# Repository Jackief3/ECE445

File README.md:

# Water Quality Management System

The goal of the project is to manage water quality for life in aquatic environments.

Team members:
- Jackie Fang
- Harrison Griggs
- Haokai Liu

## Results

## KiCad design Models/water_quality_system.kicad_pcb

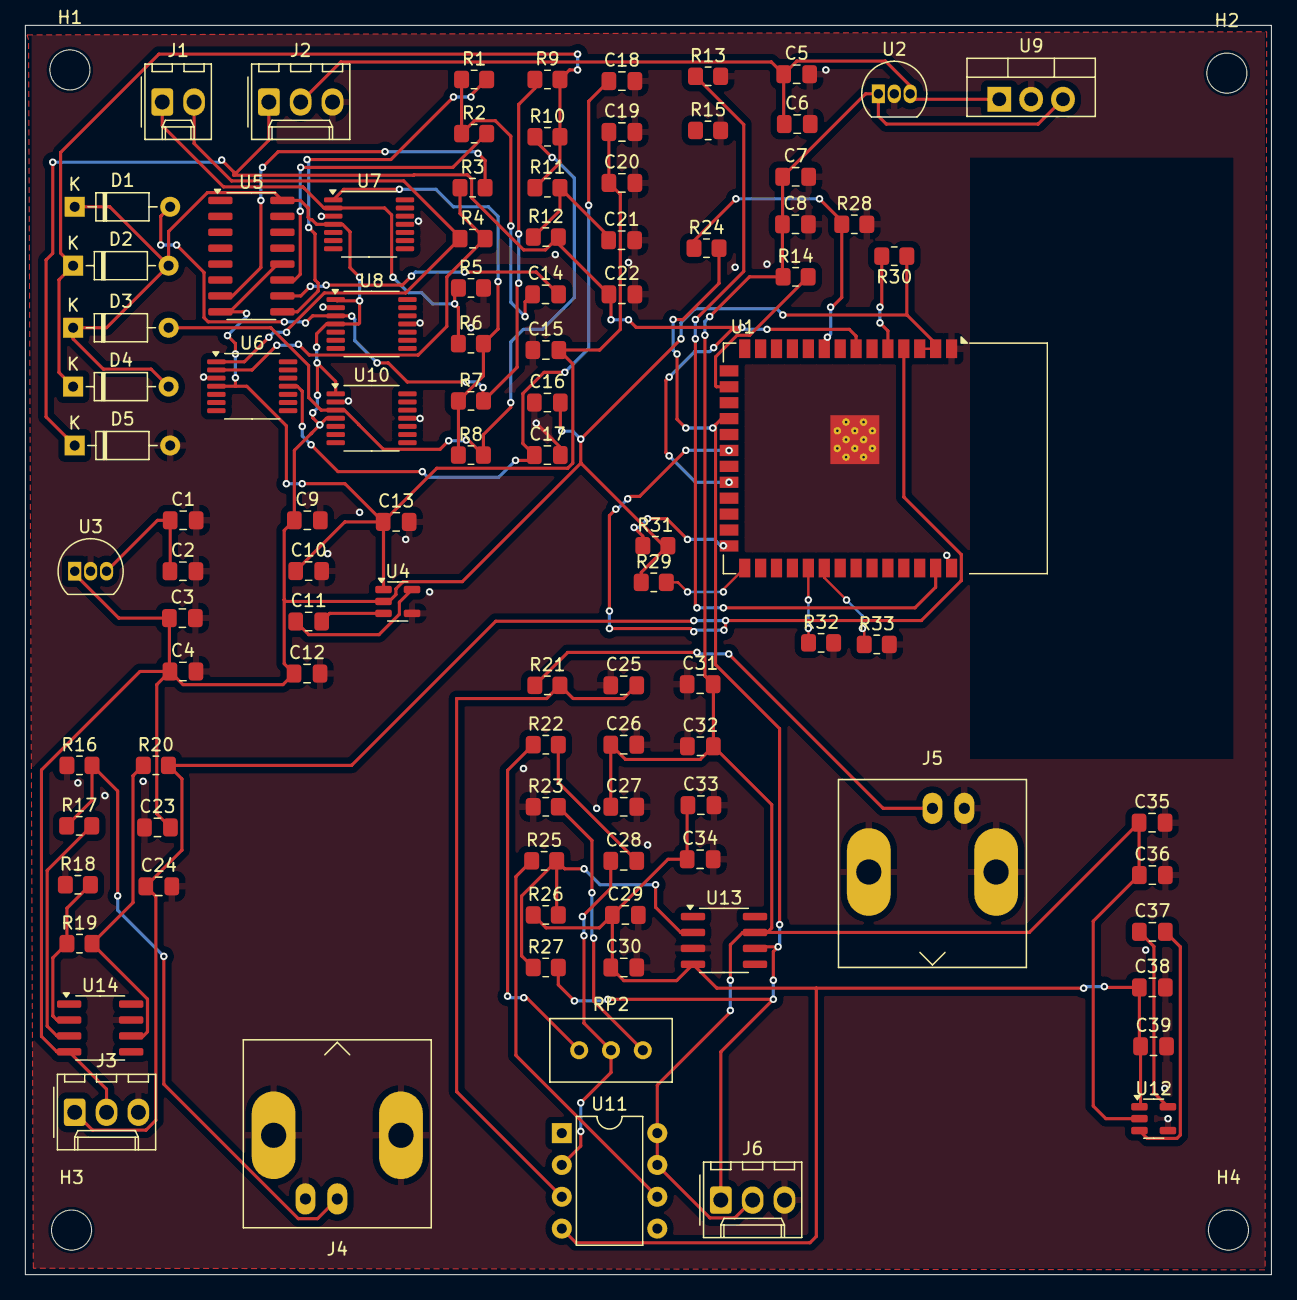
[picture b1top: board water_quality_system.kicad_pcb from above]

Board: 2 copper layers, 99.4 x 99.7 mm, 102 parts (0 on the bottom side), 48 nets.

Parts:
C1, C3, C5, C7, C12, C13, C27, C30, C33, C35, C38: 10uF; C_0805_2012Metric_Pad1.18x1.45mm_HandSolder
C2, C4, C6, C8, C9, C10, C15, C16, C17, C20, C26, C29, C34, C36, C39: 100nF; C_0805_2012Metric_Pad1.18x1.45mm_HandSolder
C11, C37: 2.2uF; C_0805_2012Metric_Pad1.18x1.45mm_HandSolder
C14, C21, C22, C28: 1nF; C_0805_2012Metric_Pad1.18x1.45mm_HandSolder
C18, C19: 4.7nF; C_0805_2012Metric_Pad1.18x1.45mm_HandSolder
C23, C24, C31: 10nF; C_0805_2012Metric_Pad1.18x1.45mm_HandSolder
C25: 2.2nF; C_0805_2012Metric_Pad1.18x1.45mm_HandSolder
C32: 100uF; C_0805_2012Metric_Pad1.18x1.45mm_HandSolder
D1, D2, D3, D4, D5: 1N4148; D_DO-35_SOD27_P7.62mm_Horizontal
H1, H2, H3, H4: MountingHole; MountingHole_3.2mm_M3
J1: Conn_01x02; Molex_KK-254_AE-6410-02A_1x02_P2.54mm_Vertical
J2, J3, J6: Conn_01x03; Molex_KK-254_AE-6410-03A_1x03_P2.54mm_Vertical
J4, J5: Conn_Coaxial; BNC_Amphenol_B6252HB-NPP3G-50_Horizontal
R1, R3: 100k; R_0805_2012Metric_Pad1.20x1.40mm_HandSolder
R2, R7, R8, R9, R10, R11, R12: 10k; R_0805_2012Metric_Pad1.20x1.40mm_HandSolder
R4: 6.8k; R_0805_2012Metric_Pad1.20x1.40mm_HandSolder
R5: 1M; R_0805_2012Metric_Pad1.20x1.40mm_HandSolder
R6: 5.6k; R_0805_2012Metric_Pad1.20x1.40mm_HandSolder
R13, R14, R17, R21: 4.7k; R_0805_2012Metric_Pad1.20x1.40mm_HandSolder
R15: 470; R_0805_2012Metric_Pad1.20x1.40mm_HandSolder
R16: 7.5k; R_0805_2012Metric_Pad1.20x1.40mm_HandSolder
R18: 8.2k; R_0805_2012Metric_Pad1.20x1.40mm_HandSolder
R19: 300k; R_0805_2012Metric_Pad1.20x1.40mm_HandSolder
R20: 220; R_0805_2012Metric_Pad1.20x1.40mm_HandSolder
R22: 2.2k; R_0805_2012Metric_Pad1.20x1.40mm_HandSolder
R23: 1k; R_0805_2012Metric_Pad1.20x1.40mm_HandSolder
R24: 1.8k; R_0805_2012Metric_Pad1.20x1.40mm_HandSolder
R25, R27: 30k; R_0805_2012Metric_Pad1.20x1.40mm_HandSolder
R26: 75k; R_0805_2012Metric_Pad1.20x1.40mm_HandSolder
R28: 3.3k; R_0805_2012Metric_Pad1.20x1.40mm_HandSolder
R29, R30, R31, R32, R33: R10k; R_0805_2012Metric_Pad1.20x1.40mm_HandSolder
RP2: 5k; Potentiometer_Bourns_3296W_Vertical
U1: ESP32-S3-WROOM-1
U2: LP2950-5.0_TO92; TO-92_Inline
U3: LP2950-3.3_TO92; TO-92_Inline
U4, U12: TPS60400DBV; SOT-23-5
U5: CD4060BM; SOIC-16_3.9x9.9mm_P1.27mm
U6, U7, U8, U10: LM324PW; TSSOP-14_4.4x5mm_P0.65mm
U9: LM340T-15/NOPB; TO-220-3_Vertical
U11: CA3140; DIP-8_W7.62mm
U13: TL081BCDG4; SOIC-8_3.9x4.9mm_P1.27mm
U14: TP5551-SR; SOIC-8_3.9x4.9mm_P1.27mm

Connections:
+3.3V: C3.1, C4.1, C9.1, C12.1, C16.2, C23.2, D1.1 (K), D2.2 (A), D3.1 (K), D4.2 (A), J3.2, R29.1, R30.1, R31.2, U1.2 (3V3), U1.3 (EN), U3.1 (VO), U4.2 (IN), U5.16 (VCC), U7.4, U8.1, U8.4, U10.1, U10.4, U14.4 (VS-)
+5V: C7.1, C8.1, C26.1, C27.1, C31.2, C32.2, C35.1, C36.1, J6.2, R14.1, U2.1 (VO), U9.3 (OUT), U11.7 (V+), U11.8 (STRB), U12.2 (IN), U13.7 (VCC+)
+9V: C1.1, C2.1, U3.3 (VI)
-3.3V: C10.1, C13.1, C15.2, C19.1, C20.1, U4.1 (OUT), U5.8 (GND), U5.12 (RESET), U6.4
-5V: C29.1, C30.1, C33.1, C34.1, C38.1, C39.1, R26.1, U11.4 (V-), U12.1 (OUT), U13.4 (VCC-)
/DO_Data: C24.1, J3.1, R20.2, U1.20 (IO12)
/DQ: R14.2, U1.16 (IO46)
/PH_Data: R24.1, R28.1, U1.9 (IO16)
/TDS_Data: C22.1, D5.1 (K), J2.1, R12.2, U1.22 (IO14)
/Turbidity_Data: R13.1, U1.38 (IO2)
GND: C1.2, C2.2, C3.2, C4.2, C5.2, C6.2, C7.2, C8.2, C9.2, C10.2, C12.2, C13.2, C15.1, C16.1, C17.2, C18.2, C19.2, C20.2, C21.2, C22.2, C23.1, C24.2, C25.1, C26.2, C27.2, C29.2, C30.2, C31.1, C32.1, C33.2, C34.2, C35.2, C36.2, C38.2, C39.2, D5.2 (A), J2.3, J3.3, J4.2 (Ext), J5.2 (Ext), J6.3, R5.2, R13.2, R15.2, R16.1, R18.1, R23.1, R28.2, R32.2, R33.2, U1.1 (GND), U1.40 (GND), U1.41 (GND), U2.2 (GND), U3.2 (GND), U4.4 (GND), U6.3, U7.3, U7.11, U8.2, U8.11, U9.2 (GND), U10.2, U10.11, U12.4 (GND), U13.3 (IN+), U14.7 (VS+)
unnamed: C14.1, R1.1, R2.1
unnamed: C17.1, C18.1, U6.11
unnamed: C21.1, R11.2, R12.1
unnamed: C28.2, R22.2
unnamed: D1.2 (A), R7.2, R9.1, U8.3
unnamed: D2.1 (K), D4.1 (K), R9.2, R10.2, R11.1
unnamed: D3.2 (A), R8.2, R10.1, U10.3
unnamed: J1.1, R5.1, R6.1, U7.2
unnamed: J1.2, R4.1, U6.1
unnamed: J4.1 (In), R16.2, R17.1
unnamed: J5.1 (In), R21.1
unnamed: J6.1, R24.2, R27.2, U13.6 (OUT)
unnamed: R3.1, R4.2, U6.2
unnamed: R6.2, R7.1, R8.1, U7.1
unnamed: R22.1, RP2.3
unnamed: R23.2, RP2.1
unnamed: R25.1, U11.6
unnamed: R29.2, U1.27 (IO0)
unnamed: R30.2, U1.5 (IO5)
unnamed: R32.1, U1.31 (IO38)
unnamed: R33.1, U1.32 (IO39)
unnamed: R31.1, U1.26 (IO45)
unnamed: C11.1, U4.5 (C_{FLY+})
unnamed: C11.2, U4.3 (C_{FLY-})
unnamed: R1.2, U5.9 (EN1)
unnamed: C14.2, U5.10 (EN2)
unnamed: R2.2, U5.11 (EN3)
unnamed: R3.2, U5.7 (Q4)
unnamed: C25.2, R21.2, U11.3 (+)
unnamed: C28.1, RP2.2, U11.2 (-)
unnamed: C37.1, U12.5 (C_{FLY+})
unnamed: C37.2, U12.3 (C_{FLY-})
unnamed: R25.2, R26.2, R27.1, U13.2 (IN-)
unnamed: R17.2, U14.3 (IN+)
unnamed: R18.2, R19.1, U14.2 (IN-)
unnamed: R19.2, R20.1, U14.6 (OUT)
VCC: C5.1, C6.1, J2.2, U2.3 (VI), U9.1 (IN)

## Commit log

2025-05-08 Create Project Ideas
